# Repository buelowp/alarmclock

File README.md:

# alarmclock

A Particle project named alarmclock

## Welcome to your project!

Every new Particle project is composed of 3 important elements that you'll see have been created in your project directory for alarmclock.

#### ```/src``` folder:  
This is the source folder that contains the firmware files for your project. It should *not* be renamed. 
Anything that is in this folder when you compile your project will be sent to our compile service and compiled into a firmware binary for the Particle device that you have targeted.

If your application contains multiple files, they should all be included in the `src` folder. If your firmware depends on Particle libraries, those dependencies are specified in the `project.properties` file referenced below.

#### ```.ino``` file:
This file is the firmware that will run as the primary application on your Particle device. It contains a `setup()` and `loop()` function, and can be written in Wiring or C/C++. For more information about using the Particle firmware API to create firmware for your Particle device, refer to the [Firmware Reference](https://docs.particle.io/reference/firmware/) section of the Particle documentation.

#### ```project.properties``` file:  
This is the file that specifies the name and version number of the libraries that your project depends on. Dependencies are added automatically to your `project.properties` file when you add a library to a project using the `particle library add` command in the CLI or add a library in the Desktop IDE.

## Adding additional files to your project

#### Projects with multiple sources
If you would like add additional files to your application, they should be added to the `/src` folder. All files in the `/src` folder will be sent to the Particle Cloud to produce a compiled binary.

#### Projects with external libraries
If your project includes a library that has not been registered in the Particle libraries system, you should create a new folder named `/lib/<libraryname>/src` under `/<project dir>` and add the `.h` and `.cpp` files for your library there. All contents of the `/lib` folder and subfolders will also be sent to the Cloud for compilation.

## Compiling your project

When you're ready to compile your project, make sure you have the correct Particle device target selected and run `particle compile <platform>` in the CLI or click the Compile button in the Desktop IDE. The following files in your project folder will be sent to the compile service:

- Everything in the `/src` folder, including your `.ino` application file
- The `project.properties` file for your project
- Any libraries stored under `lib/<libraryname>/src`

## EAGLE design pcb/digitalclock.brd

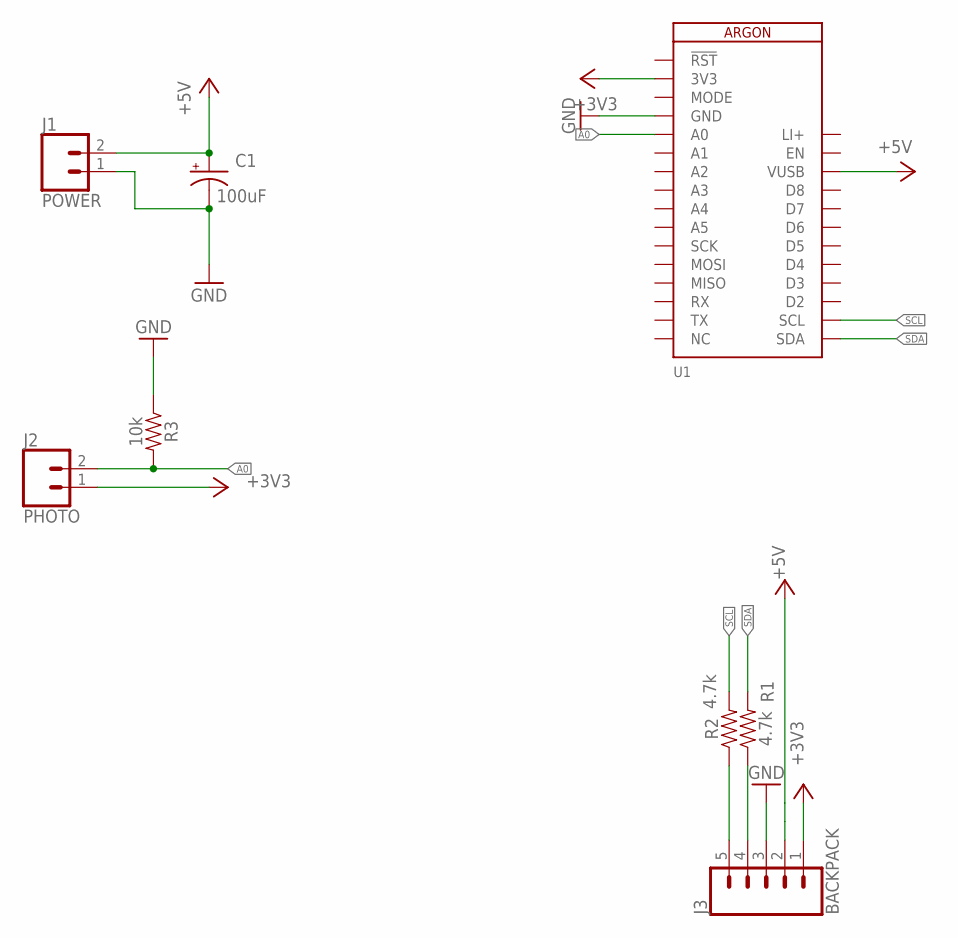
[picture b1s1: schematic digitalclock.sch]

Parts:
C1: 100uF; CPOL-RADIAL-2.5MM-6.5MM
J1: POWER; 1X02
J2: PHOTO; 1X02
J3: BACKPACK; 1X05
R1, R2: 4.7k; AXIAL-0.3
R3: 10k; AXIAL-0.3
U1: ARGON

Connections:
+3V3: J2.1, J3.1, U1.2 (3V3)
+5V: C1.1 (+), J1.2, J3.2, U1.26 (VUSB)
A0: J2.2, R3.P$2 (2), U1.5 (A0)
GND: C1.2 (-), J1.1, J3.3, R3.P$1 (1), U1.4 (GND)
LI+: U1.28 (LI+)
unnamed: J3.5, R2.P$1 (1)
unnamed: J3.4, R1.P$1 (1)
SCL: R2.P$2 (2), U1.18 (SCL)
SDA: R1.P$2 (2), U1.17 (SDA)

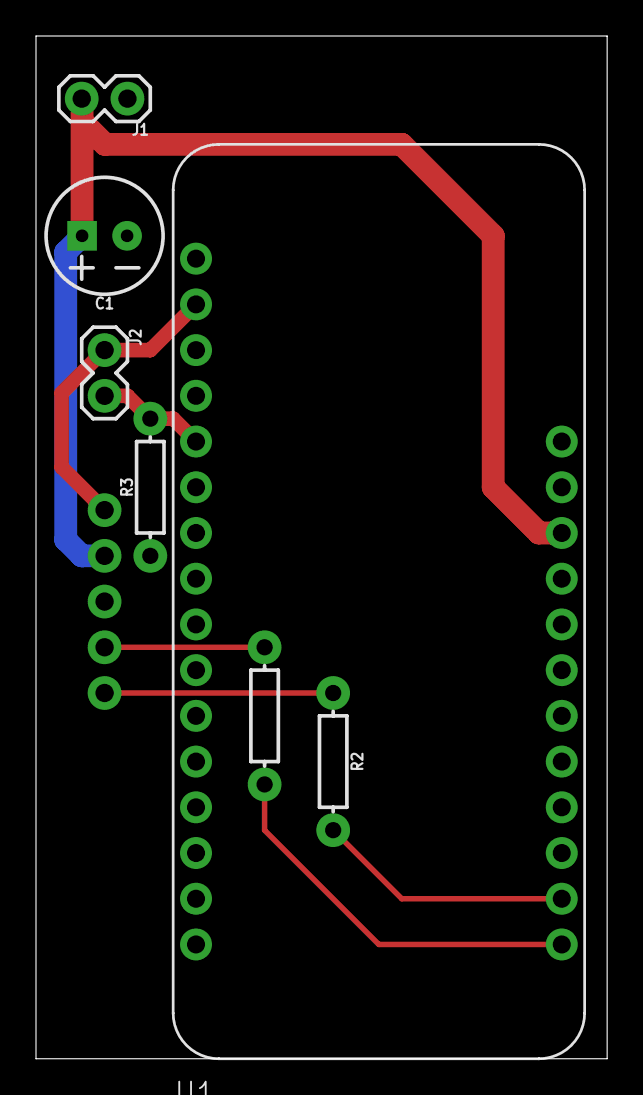
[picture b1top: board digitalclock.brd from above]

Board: 2 copper layers, 31.7 x 56.8 mm, 8 parts (1 on the bottom side), 8 nets.

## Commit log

2017-08-17 Got it working now. Needs some polish
2017-08-27 Fixed issues related to time and timzone.
    Does time right now
    Added some bitmaps to clean up where digits sit
2017-09-24 Closer to done
    Tested with new NtpClientLib content.
    Fixed crash related to old NTP logic.
2017-09-24 Disable NTP sync if we lose IP
2017-09-24 More fixups for timezone
2017-11-10 First pass at doing the alarm clock with a photon for easier updates.
2017-11-10 Got it working now. Next up, put it in a case.
2017-11-10 Fixed some bugs
    * Updated when I call the timezone update
    * Added some prints to verify it's not always asking for time
2017-11-11 Added the ability to force the brightness
2017-11-14 Fixing the midnight display bug
2018-07-07 Pushing latest
2018-11-04 Bugfixes
    Fixed some bugs with determining the correct DST offset
2021-04-28 Fixups
2021-04-28 Fixups
    * Add temp/humidity to the clock
    * Update PCB for the connections
    * Start DST settings in 2021
2021-05-07 Fixing up and removing old dead code
    * New range for brightness
    * Remove old code

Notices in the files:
parts and their libraries:
SparkFun-Capacitors: Licensing: Creative Commons ShareAlike 4.0 International - https://creativecommons.org/licenses/by-sa/4.0
Particle-Devices: Licensing: Designed by Particle.
